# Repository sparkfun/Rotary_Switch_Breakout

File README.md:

Rotary Switch Breakout
========================================

[
*SparkFun Rotary Switch Breakout (BOB-13098)*](https://www.sparkfun.com/products/13098)

This pcb breaks out pins from our 10-pin rotary switches to standard 0.1" headers. 

Repository Contents
-------------------

* **/Hardware** - All Eagle design files (.brd, .sch, .STL)

License Information
-------------------
The hardware is released under [Creative Commons ShareAlike 4.0 International](https://creativecommons.org/licenses/by-sa/4.0/).

Distributed as-is; no warranty is given.

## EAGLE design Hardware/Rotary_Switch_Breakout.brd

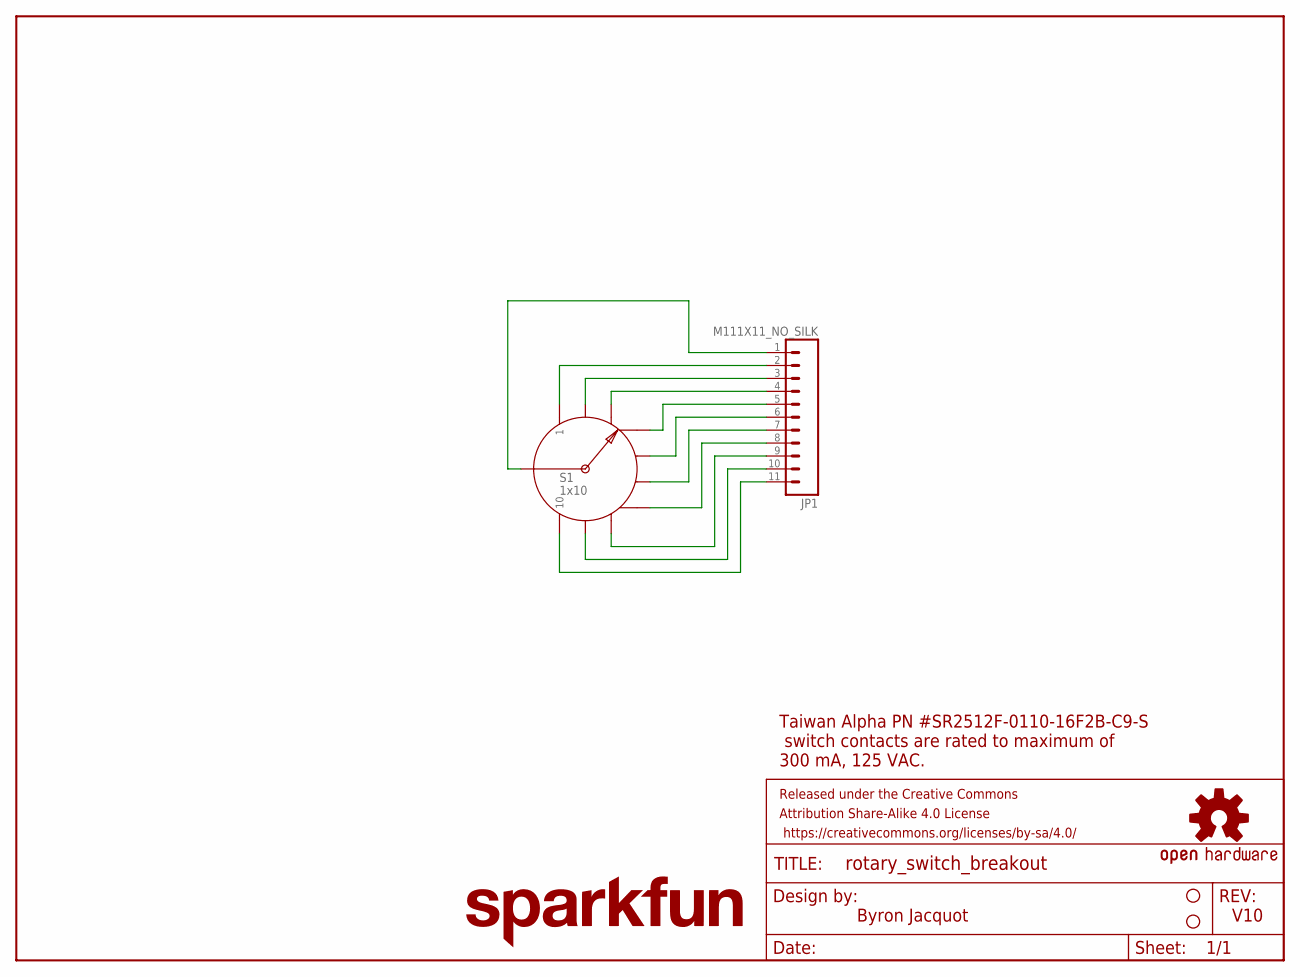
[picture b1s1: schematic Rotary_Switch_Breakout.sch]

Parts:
FRAME1: FRAME-LETTER; CREATIVE_COMMONS
JP1: M111X11_NO_SILK; 1X11_NO_SILK
LOGO1: OSHW-LOGOM; OSHW-LOGO-M
LOGO3: SFE_LOGO_NAME.1_INCH; SFE_LOGO_NAME_.1
S1: 1x10; ROTARY_SWITCH_1X10_KIT
STANDOFF2, STANDOFF4: STAND-OFF

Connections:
unnamed: JP1.1, S1.COMMON
unnamed: JP1.2, S1.1
unnamed: JP1.3, S1.2
unnamed: JP1.4, S1.3
unnamed: JP1.5, S1.4
unnamed: JP1.6, S1.5
unnamed: JP1.7, S1.6
unnamed: JP1.8, S1.7
unnamed: JP1.9, S1.8
unnamed: JP1.10, S1.9
unnamed: JP1.11, S1.10

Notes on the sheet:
Byron Jacquot
V10
Taiwan Alpha PN #SR2512F-0110-16F2B-C9-S switch contacts are rated to maximum of 300 mA, 125 VAC.

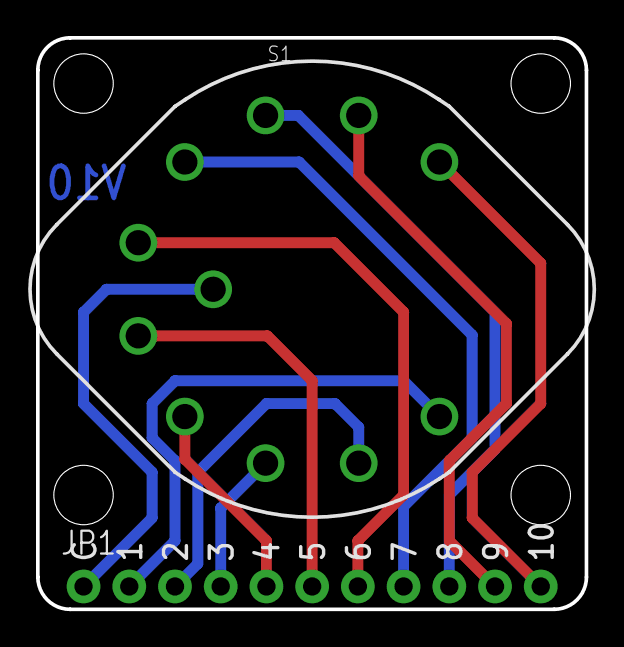
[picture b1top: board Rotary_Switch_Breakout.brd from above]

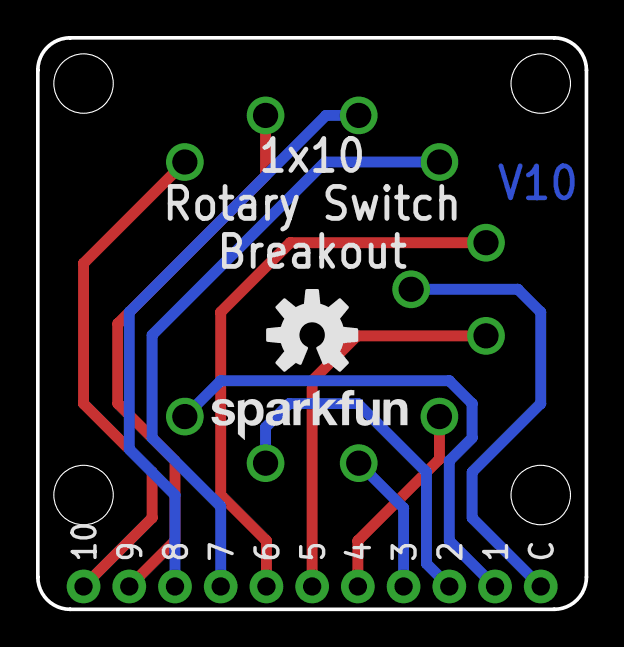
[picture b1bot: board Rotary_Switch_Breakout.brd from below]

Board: 2 copper layers, 30.5 x 31.8 mm, 9 parts (2 on the bottom side), 11 nets.

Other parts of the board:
STANDOFF1, STANDOFF3: STAND-OFF

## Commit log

2014-08-20 Initial commit
    Boilerplate and initial board design
2014-09-03 Updates to layout
2014-09-03 fixed an airwire
2014-11-05 Ready to review for reds
    Added dimensions, rolled revision # to V10
2014-11-10 Revising from review comments.
    Now has 4 standoff holes.
    Dimensioning is more legible.
2014-11-12 Updated from QC checklist review.
2015-01-07 Updating README with product links

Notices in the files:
parts and their libraries:
SparkFun-Aesthetics: Licensing: Creative Commons ShareAlike 4.0 International - https://creativecommons.org/licenses/by-sa/4.0
SparkFun-Aesthetics: Released under the Creative Commons Attribution Share-Alike 4.0 License
SparkFun-Aesthetics: Released under the Creative Commons
